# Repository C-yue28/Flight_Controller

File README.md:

<h1>Custom Flight Controller</h1>

<h3>What is it?</h3>
<p>This is a custom flight controller with onboard LiPo charging capabilities and buck converters for 3V bus as well as support for 6 external motors (3 DC, 3 servo) and 7-pin breakout for external sensor array. USB-UART bus for uploading firmware via serial. Internal power paths for limited high-current motor handling; however most motor wiring will most likely have to be done externally due to PCB limitations.</p>

<h3>Why did I make this?</h3>
<p>Flight has always been something that has fascinated me and so far my only experience has been with assembling premade drone kits or glider kits. I want to be able to go out and fly something that I made essentially from scratch. I have this vision of myself standing on the roof, tossing the plane off, and watching it fly up into the sky, and then looking at the camera feed to see the world from up high.</p>

<h3>Main components/features</h3>
<ol>
  <li>ESP32-S3-WROOM-1U - Central processor</li>
  <li>BMS management circuitry; computer is powered by 3S LiPo battery</li>
  <li>IMU (6-axis; accelerometer/gyroscope)</li>
  <li>Pressure sensor (for altitude)</li>
  <li>OV5640 Camera (external)</li>
  <li>Miscellaneous: external 2.4ghz antenna capability; dual USB-C for charging/data; external microSD support</li>
</ol>

<h3>Firmware brief description</h3>
- Modular handling of all sensors with interrupts configured to save battery power
- Verbose error/initialization logging to detect I2C issues
- Ability to log data to microSD card

<h3>Images</h3>

<h3>External sources (for the LSM6DSOX firmware libraries)</h3>

[Base LSM6DS Adafruit library](https://github.com/adafruit/Adafruit_LSM6DS/blob/master/examples/adafruit_lsm6ds_unifiedsensors/adafruit_lsm6ds_unifiedsensors.ino)

### Dependencies of this library:

[Adafruit_BusIO](https://github.com/adafruit/Adafruit_BusIO/tree/master)

[Adafruit_Sensor](https://github.com/adafruit/Adafruit_Sensor/tree/master)

<h3>BOM</h3>

| Item     | Price | Distributor/Supplier |
|----------|-------|----------------------|
| PCB      | 47.9  | JLCPCB               |
| Stencil  | 7.16  | JLCPCB               |
| Shipping | 24.15 | JLCPCB               |
| Total    | 79.21 |                      |

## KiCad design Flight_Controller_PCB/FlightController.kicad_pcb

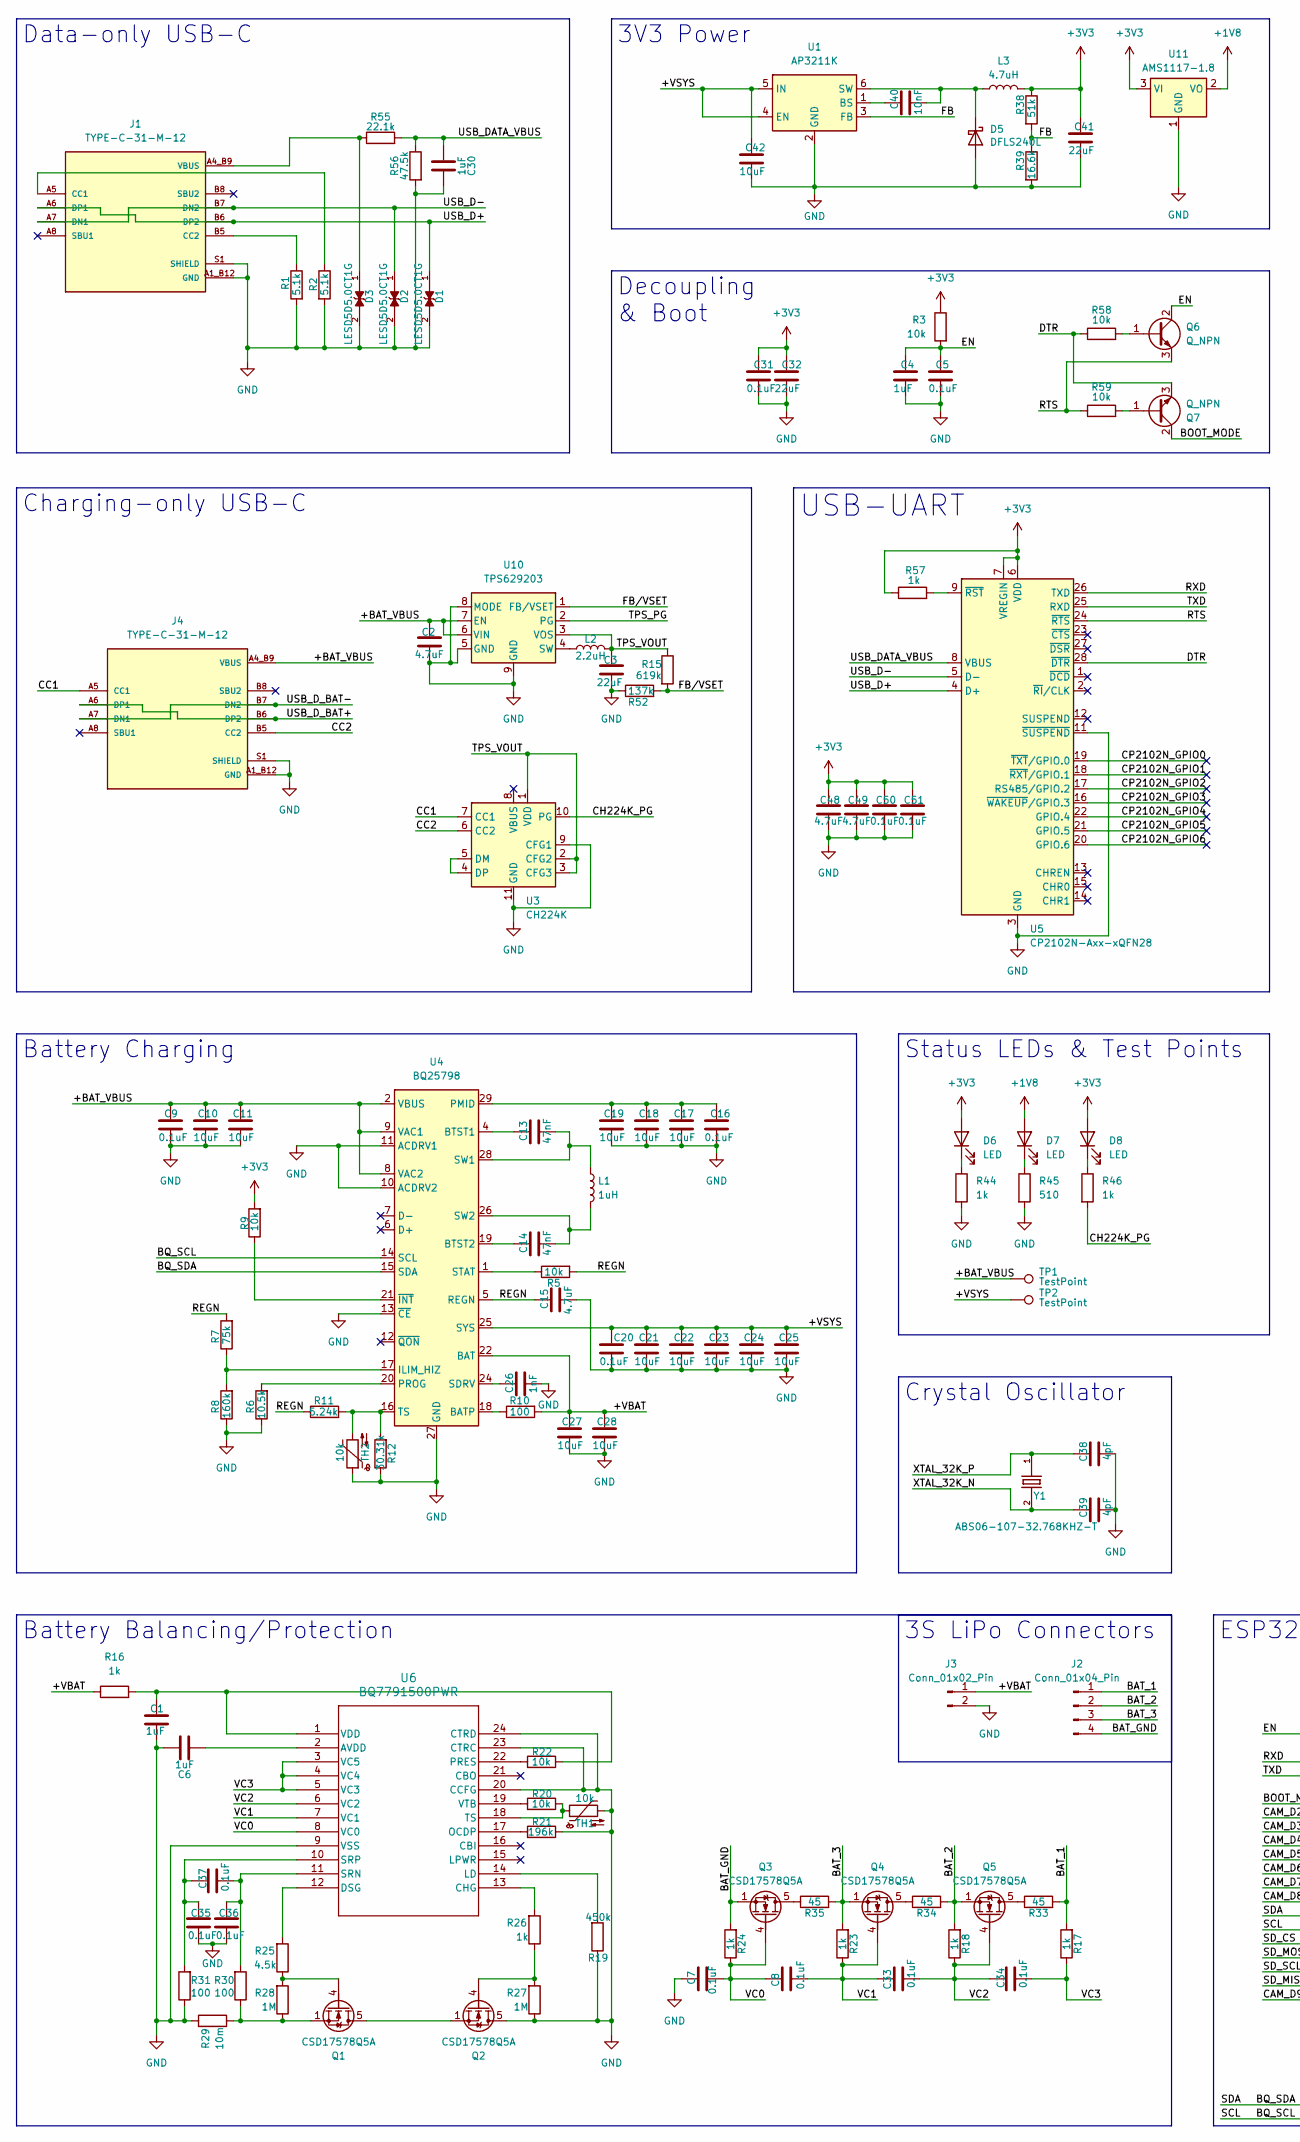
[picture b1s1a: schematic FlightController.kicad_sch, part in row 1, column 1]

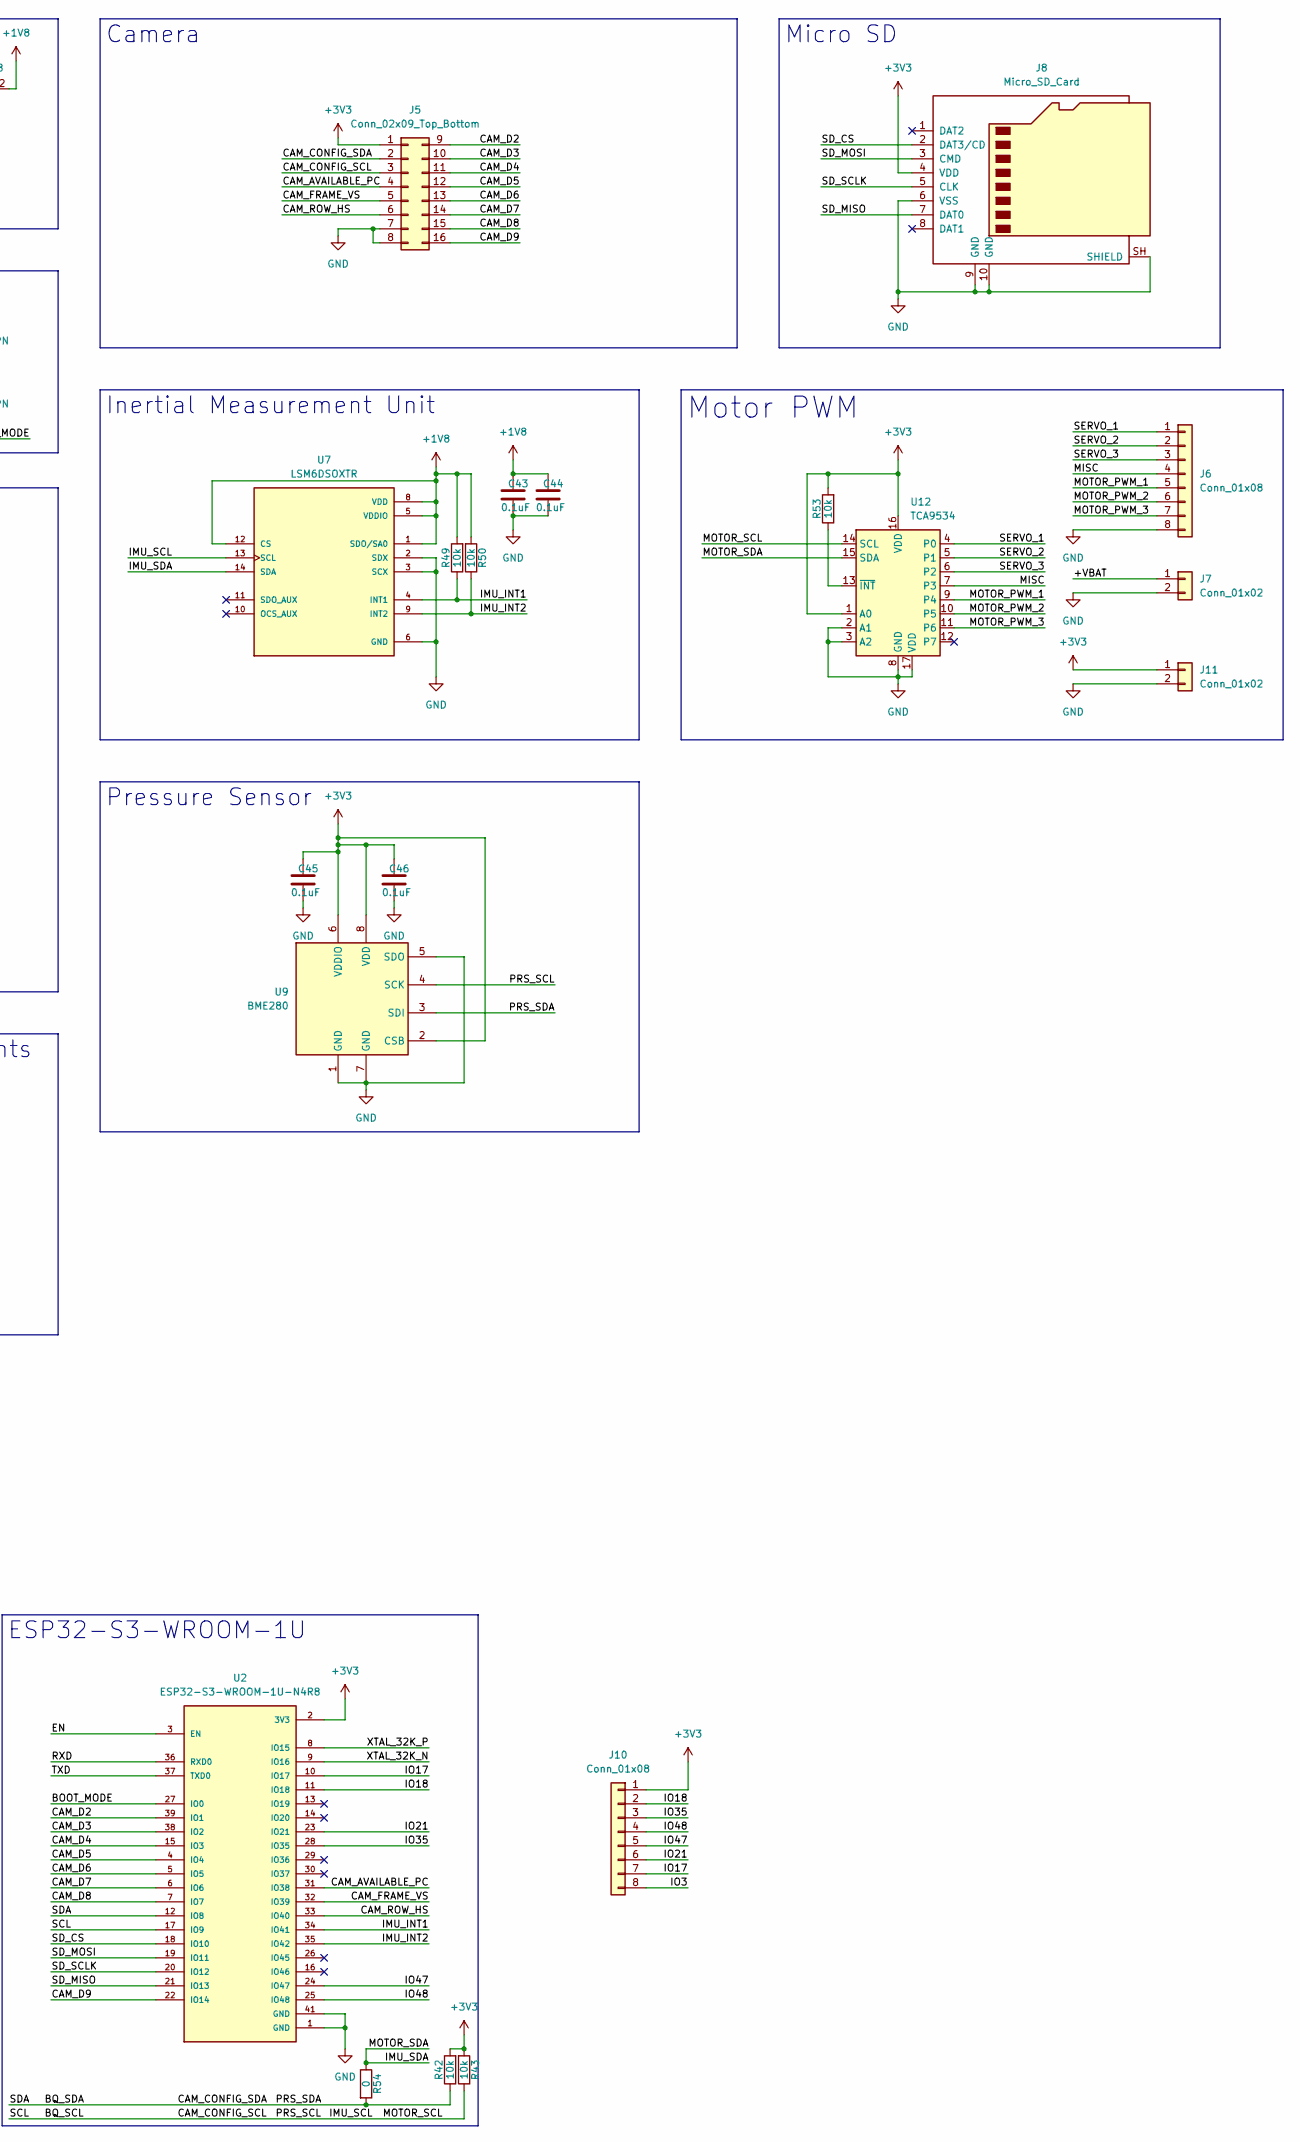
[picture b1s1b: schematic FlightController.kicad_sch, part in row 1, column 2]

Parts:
C1, C4, C6, C30: 1uF; C_0603_1608Metric
C2: 4.7uF; C_1206_3216Metric
C3: 22uF; C_0805_2012Metric
C5, C7, C8, C9, C16, C20, C31, C33, C34, C35, C36, C37, C43, C44, C45, C46, C50, C51: 0.1uF; C_0603_1608Metric
C10, C11, C17, C18, C19, C21, C22, C23, C24, C25, C27, C28, C42: 10uF; C_0603_1608Metric
C13, C14: 47nF; C_0603_1608Metric
C15, C48, C49: 4.7uF; C_0603_1608Metric
C26: 1nF; C_0603_1608Metric
C32, C41: 22uF; C_0603_1608Metric
C38, C39: 4pF; C_0603_1608Metric
C40: 10nF; C_0603_1608Metric
D1, D2, D3: LESD5D5.0CT1G; TVS_LESD5D5.0CT1G; PARTREV O
D5: DFLS240L; D_PowerDI-123
D6, D7, D8: LED; LED_0402_1005Metric
J1, J4: TYPE-C-31-M-12; HRO_TYPE-C-31-M-12; PARTREV 2020.12.08
J2: Conn_01x04_Pin; JST_XH_B4B-XH-A_1x04_P2.50mm_Vertical
J3: Conn_01x02_Pin; AMASS_XT60-M_1x02_P7.20mm_Vertical
J5: Conn_02x09_Top_Bottom; TestPoint_THTPad_2.0x2.0mm_Drill1.0mm
J6, J10: Conn_01x08; TestPoint_THTPad_4.0x4.0mm_Drill2.0mm
J7, J11: Conn_01x02; TestPoint_THTPad_4.0x4.0mm_Drill2.0mm
J8: Micro_SD_Card; microSD_HC_Molex_104031-0811
L1: 1uH; L_0603_1608Metric
L2: 2.2uH; L_1008_2520Metric
L3: 4.7uH; L_Abracon_ASPI-4030S
Q1, Q2, Q3, Q4, Q5: CSD17578Q5A; VSON-8_3.3x3.3mm_P0.65mm_NexFET
Q6, Q7: Q_NPN; SOT-23
R1, R2: 5.1k; R_0402_1005Metric
R3, R5, R9, R20, R22, R42, R43, R49, R50, R53, R58, R59: 10k; R_0402_1005Metric
R6: 10.5k; R_0402_1005Metric
R7: 75k; R_0402_1005Metric
R8: 160k; R_0402_1005Metric
R10, R30, R31: 100; R_0402_1005Metric
R11: 5.24k; R_0402_1005Metric
R12: 30.31k; R_0402_1005Metric
R15: 619k; R_0402_1005Metric
R16, R17, R18, R23, R24, R26, R44, R46, R57: 1k; R_0402_1005Metric
R19: 450k; R_0402_1005Metric
R21: 196k; R_0402_1005Metric
R25: 4.5k; R_0402_1005Metric
R27, R28: 1M; R_0402_1005Metric
R29: 10m; R_0402_1005Metric
R33, R34, R35: 45; R_0805_2012Metric_Pad1.20x1.40mm_HandSolder
R38: 51k; R_0402_1005Metric
R39: 16.6k; R_0402_1005Metric
R45: 510; R_0402_1005Metric
R52: 137k; R_0402_1005Metric
R54: 0; R_0603_1608Metric
R55: 22.1k; R_0402_1005Metric
R56: 47.5k; R_0402_1005Metric
TH1, TH2: 10k; R_0805_2012Metric
TP1, TP2: TestPoint; TestPoint_THTPad_1.5x1.5mm_Drill0.7mm
U1: AP3211K; SOT-23-6
U2: ESP32-S3-WROOM-1U-N4R8; XCVR_ESP32-S3-WROOM-1U-N4R8; PARTREV v1.1; DigiKey_Part_Number 1965-ESP32-S3-WROOM-1U-N4R8CT-ND
U3: CH224K; SSOP-10-1EP_3.9x4.9mm_P1mm_EP2.1x3.3mm
U4: BQ25798; Texas_RQM0029A_VQFN-29_4x4mm_P0.4mm
U5: CP2102N-Axx-xQFN28; QFN-28-1EP_5x5mm_P0.5mm_EP3.35x3.35mm
U6: BQ7791500PWR; PW24_TEX
U7: LSM6DSOXTR; PQFN50P250X300X86-14N; PARTREV 3.0; DigiKey_Part_Number 497-18367-1-ND
U9: BME280; Bosch_LGA-8_2.5x2.5mm_P0.65mm_ClockwisePinNumbering
U10: TPS629203; SOT-583-8
U11: AMS1117-1.8; SOT-223-3_TabPin2
U12: TCA9534; TSSOP-16-1EP_4.4x5mm_P0.65mm
Y1: ABS06-107-32.768KHZ-T; XTAL_ABS06-107-32.768KHZ-T; DigiKey_Part_Number 535-12373-1-ND

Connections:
+1V8: C43.1, C44.1, D7.2 (A), R49.2, R50.2, U7.1 (SDO/SA0), U7.5 (VDDIO), U7.8 (VDD), U7.12 (CS), U11.2 (VO)
+3V3: C31.1, C32.1, C41.1, C45.1, C46.1, C48.1, C49.1, C50.1, C51.1, D6.2 (A), D8.2 (A), J5.1, J8.4 (VDD), J10.1, J11.1, L3.2, R3.1, R9.2, R38.1, R42.2, R43.2, R53.2, R57.1, U2.2 (3V3), U5.6 (VDD), U5.7 (VREGIN), U9.2 (CSB), U9.6 (VDDIO), U9.8 (VDD), U11.3 (VI), U12.1 (A0), U12.16 (VDD)
/+VBAT: C27.1, C28.1, J3.1, J7.1, R10.2, R16.1, U4.22 (BAT), U4.23 (BAT)
/+VSYS: C20.1, C21.1, C22.1, C23.1, C24.1, C25.1, C42.1, TP2.1 (1_1), U1.4 (EN), U1.5 (IN), U4.25 (SYS)
/BAT_1: J2.1, R17.2, R33.2
/BAT_2: J2.2, Q5.1 (S), Q5.2 (S), Q5.3 (S), R18.2, R34.2
/BAT_3: J2.3, Q4.1 (S), Q4.2 (S), Q4.3 (S), R23.2, R35.2
/BAT_GND: J2.4, Q3.1 (S), Q3.2 (S), Q3.3 (S), R24.2
/BOOT_MODE: Q7.2 (C), U2.27 (IO0)
/BQ_SCL: J5.3, R43.1, U2.17 (IO9), U4.14 (SCL), U7.13 (SCL), U9.4 (SCK), U12.14 (SCL)
/BQ_SDA: J5.2, R42.1, R54.2, U2.12 (IO8), U4.15 (SDA), U9.3 (SDI)
/CAM_AVAILABLE_PC: J5.4, U2.31 (IO38)
/CAM_D2: J5.9, U2.39 (IO1)
/CAM_D3: J5.10, U2.38 (IO2)
/CAM_D4: J5.11, U2.15 (IO3)
/CAM_D5: J5.12, U2.4 (IO4)
/CAM_D6: J5.13, U2.5 (IO5)
/CAM_D7: J5.14, U2.6 (IO6)
/CAM_D8: J5.15, U2.7 (IO7)
/CAM_D9: J5.16, U2.22 (IO14)
/CAM_FRAME_VS: J5.5, U2.32 (IO39)
/CAM_ROW_HS: J5.6, U2.33 (IO40)
/CC1: J4.A5 (CC1), U3.7 (CC1)
/CC2: J4.B5 (CC2), U3.6 (CC2)
/CH224K_PG: R46.2, U3.10 (PG)
/CP2102N_GPIO0: U5.19 (~TXT/GPIO.0)
/CP2102N_GPIO1: U5.18 (~RXT/GPIO.1)
/CP2102N_GPIO2: U5.17 (RS485/GPIO.2)
/CP2102N_GPIO3: U5.16 (~WAKEUP/GPIO.3)
/CP2102N_GPIO4: U5.22 (GPIO.4)
/CP2102N_GPIO5: U5.21 (GPIO.5)
/CP2102N_GPIO6: U5.20 (GPIO.6)
/DTR: Q7.3 (E), R58.1, U5.28 (~DTR)
/EN: C4.1, C5.1, Q6.2 (C), R3.2, U2.3 (EN)
/FB: R38.2, R39.1, U1.3 (FB)
/FB/VSET: R15.2, R52.2, U10.1 (FB/VSET)
/IMU_INT1: R49.1, U2.34 (IO41), U7.4 (INT1)
/IMU_INT2: R50.1, U2.35 (IO42), U7.9 (INT2)
/IMU_SDA: R54.1, U7.14 (SDA), U12.15 (SDA)
/IO3: J10.8
/IO17: J10.7, U2.10 (IO17)
/IO18: J10.2, U2.11 (IO18)
/IO21: J10.6, U2.23 (IO21)
/IO35: J10.3, U2.28 (IO35)
/IO47: J10.5, U2.24 (IO47)
/IO48: J10.4, U2.25 (IO48)
/MISC: J6.4, U12.7 (P3)
/MOTOR_PWM_1: J6.5, U12.9 (P4)
/MOTOR_PWM_2: J6.6, U12.10 (P5)
/MOTOR_PWM_3: J6.7, U12.11 (P6)
/REGN: C15.1, R5.2, R7.2, R11.1, U4.5 (REGN)
/RTS: Q6.3 (E), R59.1, U5.24 (~RTS)
/RXD: U2.36 (RXD0), U5.26 (TXD)
/SD_CS: J8.2 (DAT3/CD), U2.18 (IO10)
/SD_MISO: J8.7 (DAT0), U2.21 (IO13)
/SD_MOSI: J8.3 (CMD), U2.19 (IO11)
/SD_SCLK: J8.5 (CLK), U2.20 (IO12)
/SERVO_1: J6.1, U12.4 (P0)
/SERVO_2: J6.2, U12.5 (P1)
/SERVO_3: J6.3, U12.6 (P2)
/TPS_PG: U10.2 (PG)
/TPS_VOUT: C3.1, L2.1, R15.1, U3.1 (VDD), U3.2 (CFG2), U3.3 (CFG3), U10.3 (VOS)
/TXD: U2.37 (TXD0), U5.25 (RXD)
/USB_D+: D1.1, J1.A6 (DP1), J1.B6 (DP2), U5.4 (D+)
/USB_D-: D2.1, J1.A7 (DN1), J1.B7 (DN2), U5.5 (D-)
/USB_DATA_VBUS: C30.2, R55.2, R56.1, U5.8 (VBUS)
/USB_D_BAT+: J4.A6 (DP1), J4.B6 (DP2)
/USB_D_BAT-: J4.A7 (DN1), J4.B7 (DN2)
/VC0: C7.2, C8.2, Q3.4 (G), R24.1, U6.8 (VC0)
/VC1: C8.1, C33.2, Q4.4 (G), R23.1, U6.7 (VC1)
/VC2: C33.1, C34.2, Q5.4 (G), R18.1, U6.6 (VC2)
/VC3: C34.1, R17.1, U6.3 (VC5), U6.4 (VC4), U6.5 (VC3)
/XTAL_32K_N: C39.1, U2.9 (IO16), Y1.2
/XTAL_32K_P: C38.1, U2.8 (IO15), Y1.1
GND: C1.2, C2.2, C3.2, C4.2, C5.2, C6.1, C7.1, C9.2, C10.2, C11.2, C15.2, C16.2, C17.2, C18.2, C19.2, C20.2, C21.2, C22.2, C23.2, C24.2, C25.2, C26.2, C27.2, C28.2, C30.1, C31.2, C32.2, C35.1, C36.1, C38.2, C39.2, C41.2, C42.2, C43.2, C44.2, C45.2, C46.2, C48.2, C49.2, C50.2, C51.2, D1.2, D2.2, D3.2, D5.2 (A), J1.A1_B12 (GND), J1.B1_A12 (GND), J1.S1 (SHIELD), J1.S2 (SHIELD), J1.S3 (SHIELD), J1.S4 (SHIELD), J3.2, J4.A1_B12 (GND), J4.B1_A12 (GND), J4.S1 (SHIELD), J4.S2 (SHIELD), J4.S3 (SHIELD), J4.S4 (SHIELD), J5.7, J5.8, J6.8, J7.2, J8.6 (VSS), J8.9 (GND), J8.10 (GND), J8.SH (SHIELD), J11.2, Q2.5 (D), R1.2, R2.2, R6.1, R8.1, R12.1, R19.1, R21.1, R27.1, R29.2, R31.1, R39.2, R44.2, R45.2, R52.1, R56.2, TH1.2, TH2.1, U1.2 (GND), U2.1 (GND), U2.40 (GND), U2.41 (GND), U2.41_1 (GND), U2.41_2 (GND), U2.41_3 (GND), U2.41_4 (GND), U2.41_5 (GND), U2.41_6 (GND), U2.41_7 (GND), U2.41_8 (GND), U2.41_9 (GND), U3.9 (CFG1), U3.11 (GND), U4.10 (ACDRV2), U4.11 (ACDRV1), U4.13 (~CE), U4.27 (GND), U5.3 (GND), U5.11 (~SUSPEND), U5.29 (GND), U6.9 (VSS), U6.20 (CCFG), U6.23 (CTRC), U6.24 (CTRD), U7.2 (SDX), U7.3 (SCX), U7.6 (GND), U7.7 (GND), U9.1 (GND), U9.5 (SDO), U9.7 (GND), U10.5 (GND), U10.8 (MODE), U10.9 (GND), U11.1 (GND), U12.2 (A1), U12.3 (A2), U12.8 (GND), U12.17 (VDD)
unnamed: C40.2, D5.1 (K), L3.1, U1.6 (SW)
unnamed: D6.1 (K), R44.1
unnamed: D7.1 (K), R45.1
unnamed: D8.1 (K), R46.1
unnamed: J1.A5 (CC1), R2.1
unnamed: J1.B5 (CC2), R1.1
unnamed: Q1.5 (D), Q2.1 (S), Q2.2 (S), Q2.3 (S)
unnamed: Q1.4 (G), R25.1, R28.2
unnamed: Q1.1 (S), Q1.2 (S), Q1.3 (S), R28.1, R29.1, R30.1
unnamed: Q2.4 (G), R26.1, R27.2
unnamed: Q3.5 (D), R35.1
unnamed: Q4.5 (D), R34.1
unnamed: Q5.5 (D), R33.1
unnamed: Q6.1 (B), R58.2
unnamed: Q7.1 (B), R59.2
unnamed: C40.1, U1.1 (BS)
unnamed: U3.4 (DP), U3.5 (DM)
unnamed: R10.1, U4.18 (BATP)
unnamed: C13.1, U4.4 (BTST1)
unnamed: C14.1, U4.19 (BTST2)
unnamed: R7.1, R8.2, U4.17 (ILIM_HIZ)
unnamed: C16.1, C17.1, C18.1, C19.1, U4.29 (PMID)
unnamed: R6.2, U4.20 (PROG)
unnamed: C26.1, U4.24 (SDRV)
unnamed: R5.1, U4.1 (STAT)
unnamed: C13.2, L1.1, U4.28 (SW1)
unnamed: C14.2, L1.2, U4.26 (SW2)
unnamed: R11.2, R12.2, TH2.2, U4.16 (TS)
unnamed: R9.1, U4.21 (~INT)
unnamed: R57.2, U5.9 (~RST)
unnamed: C6.2, U6.2 (AVDD)
unnamed: R26.2, U6.13 (CHG)
unnamed: R25.2, U6.12 (DSG)
unnamed: R19.2, U6.14 (LD)
unnamed: R21.2, U6.17 (OCDP)
unnamed: R22.2, U6.22 (PRES)
unnamed: C36.2, C37.1, R30.2, U6.11 (SRN)
unnamed: C35.2, C37.2, R31.2, U6.10 (SRP)
unnamed: R20.1, TH1.1, U6.18 (TS)
unnamed: C1.1, R16.2, R22.1, U6.1 (VDD)
unnamed: R20.2, U6.19 (VTB)
unnamed: L2.2, U10.4 (SW)
unnamed: R53.1, U12.13 (~INT)

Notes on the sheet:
3S LiPo Connectors
ESP32-S3-WROOM-1U
Micro SD
Motor PWM
Camera
USB-UART
Decoupling & Boot
Data-only USB-C
Inertial Measurement Unit
Pressure Sensor
Battery Balancing/Protection
Battery Charging
3V3 Power
Charging-only USB-C
Crystal Oscillator
Status LEDs & Test Points

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
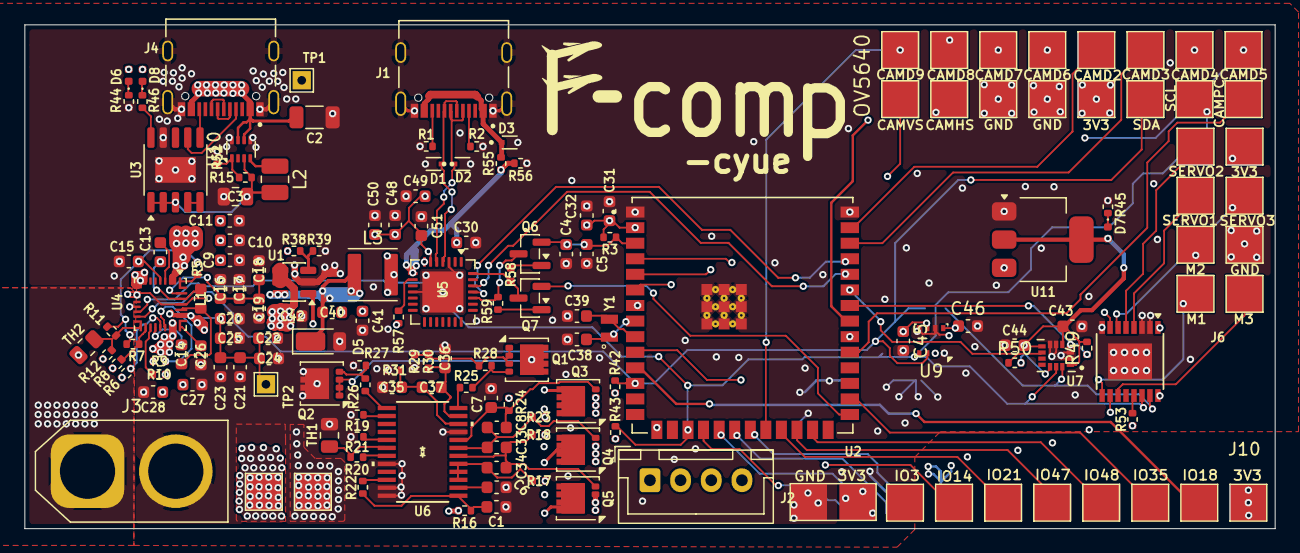
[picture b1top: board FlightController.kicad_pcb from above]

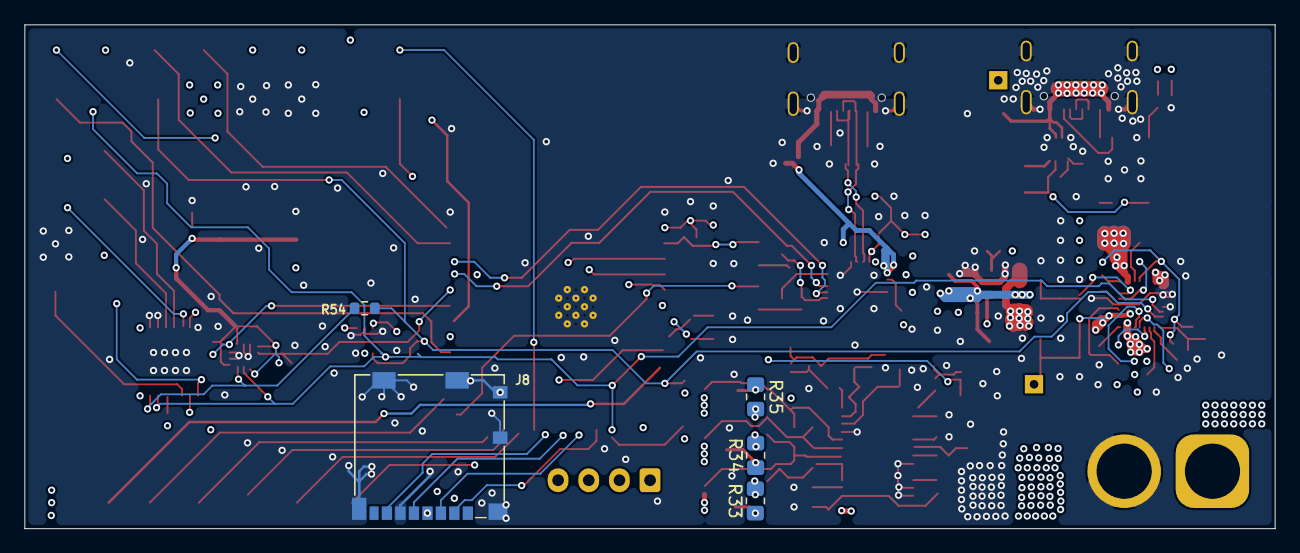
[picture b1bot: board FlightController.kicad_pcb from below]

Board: 6 copper layers, 102.0 x 41.1 mm, 139 parts (5 on the bottom side), 110 nets.

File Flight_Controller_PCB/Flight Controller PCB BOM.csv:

Designator,Footprint,Quantity,Value,URL,Cost,Notes
"C1, C30, C4, C6",0603,4,1uF,https://www.lcsc.com/product-detail/C128624.html,1.3,I may already have these
"C10, C11, C17, C18, C19, C21, C22, C23, C24, C25, C27, C28, C42",0603,13,10uF,https://www.lcsc.com/product-detail/C22367825.html,1.16,I may already have these
"C13, C14",0603,2,47nF,0603B473K500NT | FH | Price | In Stock | LCSC Electronics,0.61,
"C15, C48, C49",0603,3,4.7uF,https://www.lcsc.com/product-detail/C5252400.html?lcsc_vid=R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,0.45,I may already have these
"C16, C20, C31, C33, C34, C35, C36, C37, C43, C44, C45, C46, C5, C50, C51, C7, C8, C9",0603,18,0.1uF,https://www.lcsc.com/product-detail/C125205.html?lcsc_vid=RQ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,0.81,I may already have these
C2,1206,1,4.7uF,https://www.lcsc.com/product-detail/C22399656.html,0.85,
C26,0603,1,1nF,https://www.lcsc.com/product-detail/C44369.html,0.52,
C3,0805,1,22uF,(included below),n/a,I decided to just use a smaller footprint to save some money
"C32, C41",0603,2,22uF,https://www.digikey.com/en/products/detail/samsung-electro-m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,0.64,
"C38, C39",0603,2,4pF,https://www.lcsc.com/product-detail/C1668.html,0.42,
C40,0603,1,10nF,https://www.lcsc.com/product-detail/C100042.html,0.61,
"D1, D2, D3",TVS_LESD5D5.0CT1G,3,LESD5D5.0CT1G,https://www.lcsc.com/product-detail/C5246195.html,0.36,
D5,D_PowerDI-123,1,DFLS240L,,,
"D6, D7, D8",0402,3,LED,https://www.lcsc.com/product-detail/Light-Emitting-Diodes-LE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,0.76,
"J1, J4",HRO_TYPE-C-31-M-12,2,TYPE-C-31-M-12,(I already have these),n/a,
"J10, J6",TestPoint_THTPad_4.0x4.0mm_Drill2.0mm,2,Conn_01x08,n/a,,
"J11, J7",TestPoint_THTPad_4.0x4.0mm_Drill2.0mm,2,Conn_01x02,n/a,,
J2,JST_XH_B4B-XH-A_1x04_P2.50mm_Vertical,1,Conn_01x04_Pin,https://www.lcsc.com/product-detail/C144395.html,0.58,
J3,AMASS_XT60-M_1x02_P7.20mm_Vertical,1,Conn_01x02_Pin,https://www.lcsc.com/product-detail/C98733.html,0.4,
J5,TestPoint_THTPad_2.0x2.0mm_Drill1.0mm,1,Conn_02x09_Top_Bottom,n/a,,
J8,microSD_HC_Molex_104031-0811,1,Micro_SD_Card,https://www.lcsc.com/product-detail/C585350.html,0.68,
L1,0603,1,1uH,https://www.lcsc.com/product-detail/C5443610.html,0.42,
L2,1008,1,2.2uH,https://www.digikey.com/en/products/detail/shenzhen-sunlord-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,0.33,
L3,L_Abracon_ASPI-4030S,1,4.7uH,https://www.digikey.com/en/products/detail/abracon-llc/ASPI-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,0.27,
"Q1, Q2, Q3, Q4, Q5",VSON-8_3.3x3.3mm_P0.65mm_NexFET,5,CSD17578Q5A,https://www.lcsc.com/product-detail/C2871447.html,2.41,
"Q6, Q7",SOT-23,2,Q_NPN,https://www.lcsc.com/product-detail/C49581.html,0.79,
"R1, R2",0402,2,5.1k,https://www.digikey.com/en/products/detail/yageo/RC0402FR-07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,0.2,
"R10, R30, R31",0402,3,100,https://www.digikey.com/en/products/detail/vishay-dale/RCA04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,0.3,
R11,0402,1,5.24k,https://www.digikey.com/en/products/detail/bourns-inc/CR0402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,0.1,
R12,0402,1,30.31k,https://www.digikey.com/en/products/detail/vishay-dale/RCS04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,0.13,
R15,0402,1,619k,https://www.digikey.com/en/products/detail/stackpole-electro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,0.1,
"R16, R17, R18, R23, R24, R26, R44, R46, R57",0402,9,1k,https://www.digikey.com/en/products/detail/vishay/MCS04020C1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,0.28,I may already have these
R19,0402,1,450k,https://www.digikey.com/en/products/detail/vishay-dale/CRCW0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,0.1,
"R20, R22, R3, R42, R43, R49, R5, R50, R53, R58, R59, R9",0402,12,10k,https://www.digikey.com/en/products/detail/vishay-dale/RCA04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,0.66,I may already have these
R21,0402,1,196k,https://www.digikey.com/en/products/detail/stackpole-electro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,0.1,
R25,0402,1,4.5k,http://digikey.com/en/products/detail/vishay-dale/TNPW04024K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,0.26,
"R27, R28",0402,2,1M,https://www.digikey.com/en/products/detail/yageo/RC0402FR-07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,0.2,
R29,0402,1,10m,https://www.digikey.com/en/products/detail/thin-film-technol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,0.28,
"R33, R34, R35",0805,3,45,"MBB02070C4539FRP00 (1W, 45.3 OHM): https://www.mouser.com/c/passive-components/resistors/?power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",1.14,
R38,0402,1,51k,https://www.digikey.com/en/products/detail/stackpole-electro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,0.1,
R39,0402,1,16.6k,https://www.digikey.com/en/products/detail/vishay-dale/CRCW0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,0.1,
R45,0402,1,510,https://www.digikey.com/en/products/detail/koa-speer-electro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,0.1,
R52,0402,1,137k,https://www.digikey.com/en/products/detail/yageo/RC0402FR-07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,0.1,
R54,0603,1,0,n/a,,
R55,0402,1,22.1k,https://www.digikey.com/en/products/detail/yageo/RT0402FRE07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,0.1,
R56,0402,1,47.5k,https://www.digikey.com/en/products/detail/yageo/RC0402FR-07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,0.1,
R6,0402,1,10.5k,https://www.digikey.com/en/products/detail/yageo/RT0402FRE07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,0.1,
R7,0402,1,75k,https://www.digikey.com/en/products/detail/yageo/RT0402DRE07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,0.1,
R8,0402,1,160k,https://www.digikey.com/en/products/detail/stackpole-electro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,0.1,
"TH1, TH2",0805,2,10k,https://www.digikey.com/en/products/detail/tdk/B57471V2103J0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,0.62,
"TP1, TP2",TestPoint_THTPad_1.5x1.5mm_Drill0.7mm,2,TestPoint,n/a,,
U1,SOT-23-6,1,AP3211K,https://www.digikey.com/en/products/detail/diodes-incorporat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,0.25,I may already have this
U10,SOT-583-8,1,TPS629203,https://www.digikey.com/en/products/detail/texas-instruments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,1.08,
U11,SOT-223-3_TabPin2,1,AMS1117-1.8,https://www.digikey.com/en/products/detail/evvo/AMS1117-1-8/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,0.3,
U12,TSSOP-16-1EP_4.4x5mm_P0.65mm,1,TCA9534,https://www.digikey.com/en/products/detail/texas-instruments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,1.53,
U2,XCVR_ESP32-S3-WROOM-1U-N4R8,1,ESP32-S3-WROOM-1U-N4R8,https://www.digikey.com/en/products/detail/espressif-systems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,6.76,
U3,SSOP-10-1EP_3.9x4.9mm_P1mm_EP2.1x3.3mm,1,CH224K,https://www.lcsc.com/product-detail/C970725.html,0.62,
U4,Texas_RQM0029A_VQFN-29_4x4mm_P0.4mm,1,BQ25798,https://www.digikey.com/en/products/detail/texas-instruments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,5.2,
U5,QFN-28-1EP_5x5mm_P0.5mm_EP3.35x3.35mm,1,CP2102N-Axx-xQFN28,https://www.digikey.com/en/products/detail/silicon-labs/CP21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,5.1,
U6,PW24_TEX,1,BQ7791500PWR,https://www.digikey.com/en/products/detail/texas-instruments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,2.05,
U7,PQFN50P250X300X86-14N,1,LSM6DSOXTR,https://estore.st.com/en/lsm6dsotr-cpn.html,5.32,LSM6DSOTR
U9,Bosch_LGA-8_2.5x2.5mm_P0.65mm_ClockwisePinNumbering,1,BME280,https://www.digikey.com/en/products/detail/bosch-sensortec/B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,4,
Y1,XTAL_ABS06-107-32.768KHZ-T,1,ABS06-107-32.768KHZ-T,https://www.digikey.com/en/products/detail/abracon-llc/ABS06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,0.83,
,,,,,52.78,

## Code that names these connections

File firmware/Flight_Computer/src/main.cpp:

#include <Arduino.h>
#include <Wire.h>
#include <SD.h>
#include <SPI.h>

// Personal libraries
#include <BQ25798.h>
#include <TCA9534.h>
#include <OV5640.h>
#include <BME280.h>

// Open-source libraries
#include <Adafruit_LSM6DSOX.h>

#define ESP32_ADDR 0x67

// I2C pins

#define SDA 8
#define SCL 9

#define NUM_I2C_DEVICES 5
#define MAX_I2C_INIT_LOOPS 10

// External SD card

#define SD_CS 10
#define SD_MOSI 11
#define SD_SCK 12
#define SD_MISO 13

// Camera: OV5640

#define CAM_D2 1
#define CAM_D3 2
#define CAM_D4 3
#define CAM_D5 4
#define CAM_D6 5
#define CAM_D7 6
#define CAM_D8 7
#define CAM_D9 14
#define CAM_AVAIL_PC 38
#define CAM_FRAME_VS 39
#define CAM_ROW_HS 40

// IMU: LSM6DSOX
#define IMU_I2C_ADDR 0b1101011

#define IMU_INT1 41
#define IMU_INT2 42

// Motor handling
#define SERVO_1 0
#define SERVO_2 1
#define SERVO_3 2
#define MOTOR_1 4
#define MOTOR_2 5
#define MOTOR_3 6

#define PWM_FREQUENCY 1 // 1 tick, or 1 ms per bit on the output lines to ESC

// I2C  

BQ25798 charger(&Wire);
TCA9534 motorController(&Wire);
BME280 bme280(&Wire);
Adafruit_LSM6DSOX imu;
Adafruit_Sensor *imu_temp, *imu_gyro, *imu_accel;

sensors_vec_t rotation;
sensors_vec_t acceleration;
sensors_event_t imu_temp_event;

TaskHandle_t pwmHandle = NULL;

typedef struct {
  uint8_t pin;
  float pwm_duty;
} motorControlConfig;

bool initI2C();
int detectI2CDevices();

bool writeFile(const char *path, const char *data, bool overwrite = false);
uint8_t* readFile(const char *path);

void readIMUData(uint8_t intNum);
void outputPWM(void *pvParameters);

void setup() {

  Serial.begin(115200);
  while (!Serial);

  Serial.print("Serial initialized\n");

  if (!initI2C()) {
    Serial.println("I2C initialization failed");
    return;
  }
  Serial.println("I2C initialized");

  // SD card

  if (!SD.begin(SD_CS)) {
    Serial.println("SD initialization failed");
    return;
  } else {
    Serial.println("SD initialized successfully");
  }

  // run the motors at 25% speed
  motorControlConfig* initial_pwm_config = new motorControlConfig();
  initial_pwm_config->pwm_duty = 0.25;
  for (int i = MOTOR_1; i < MOTOR_3; i++) {
    initial_pwm_config->pin = i;
    xTaskCreatePinnedToCore(outputPWM, "PWM", 4096, (void*)initial_pwm_config, 1, NULL, 0);
  }

}

// Unit tests

/* OV5640

void loop() {
  camera_fb_t *fb = esp_camera_fb_get();
  
  if (!fb) {
      Serial.println("Camera capture failed!");
      delay(1000);
      return;
  }

  Serial.printf("Captured image! Size: %d bytes, Width: %d, Height: %d\n", fb->len, fb->width, fb->height);

  esp_camera_fb_return(fb); 
  
  delay(100); 
}

*/

/* Motors

void loop() {
  motorControlConfig* cfg = new motorControlConfig();
  cfg->pwm_duty = 0.5;
  for (int i = MOTOR_1; i < MOTOR_3; i++) {
    cfg->pin = i;
    xTaskCreatePinnedToCore(outputPWM, "PWM", 4096, cfg, 1, NULL, 0);
  }
  
  cfg->pwm_duty = 0.0;
  for (int i = MOTOR_1; i < MOTOR_3; i++) {
    cfg->pin = i;
    xTaskCreatePinnedToCore(outputPWM, "PWM", 4096, cfg, 1, NULL, 0);
  }
}

*/

/* BME280

void loop() {
  Serial.printf("Temperature: %f C\n", bme280.getTemperature());
  Serial.printf("Pressure: %f Pa\n", bme280.getPressure());
  Serial.printf("Humidity: %f %%\n", bme280.getHumidity());
  vTaskDelay(2000 / portTICK_PERIOD_MS);
}

*/

/* IMU

void loop() {
  Serial.printf("Temperature: %f C\n", altimeter.getTemperature() + imu_temp_event.temperature);
  Serial.printf("Rotation: %f rad/s, %f rad/s, %f rad/s\n", rotation.x, rotation.y, rotation.z);
  Serial.printf("Acceleration: %f m/s^2, %f m/s^2, %f m/s^2\n", acceleration.x, acceleration.y, acceleration.z);
  vTaskDelay(2000 / portTICK_PERIOD_MS);
}

*/

bool initI2C() {
  bool success_I2C = Wire.begin(SDA, SCL);
  if (success_I2C) {
    Serial.println("I2C initialized");
  } else {
    Serial.println("I2C initialization failed");
    return false;
  }

  int numDevices = detectI2CDevices();
  int loops = 0;
  while (numDevices < NUM_I2C_DEVICES) {
    Serial.printf("%d devices found\n", numDevices);
    Serial.println("Not enough I2C devices found, rechecking in 5 seconds");
    delay(5000);
    numDevices = detectI2CDevices();
    loops++;
    if (loops > MAX_I2C_INIT_LOOPS) {
      Serial.println("Max I2C init loops reached, stopping program");
      return false;
    }
  }
  Serial.printf("Successfully detected %d devices!\n", numDevices);

  // I2C device initialization

  // BQ25798

  if (charger.begin()) {
    Serial.println("BQ25798 initialized");
  } else {
    Serial.println("BQ25798 initialization failed");
    return false;
  }

  if (charger.initialize3SDefaults()) {
    Serial.println("BQ25798 3S defaults initialized");
  } else {
    Serial.println("BQ25798 3S defaults initialization failed");
    return false;
  }

  // OV5640

  if (initializeCamera(
    CAM_D2, CAM_D3, CAM_D4, CAM_D5,
    CAM_D6, CAM_D7, CAM_D8, CAM_D9,
    CAM_AVAIL_PC, CAM_FRAME_VS, CAM_ROW_HS,
    SDA, SCL,
    -1, -1
  )) {
    Serial.println("OV5640 initialized");
  } else {
    Serial.println("OV5640 initialization failed");
    return false;
  }

  // TCA9534
  motorController.begin();
  Serial.println("TCA9534 initialized");

  // BME280
  bme280.begin();
  Serial.println("BME280 initialized");

  // IMU
  if (!imu.begin_I2C(IMU_I2C_ADDR)) {
    Serial.println("Failed to initialize IMU!");
    return false;
  }
  Serial.println("IMU initialized");

  imu.configIntOutputs(true, true);
  imu.configInt1(true, true, false, false, false);
  imu.configInt2(false, false, true);

  pinMode(IMU_INT1, OUTPUT_OPEN_DRAIN | INPUT);
  pinMode(IMU_INT2, OUTPUT_OPEN_DRAIN | INPUT);

  attachInterrupt(digitalPinToInterrupt(IMU_INT1), []() { readIMUData(0x00); }, LOW);
  attachInterrupt(digitalPinToInterrupt(IMU_INT2), []() { readIMUData(0x01); }, LOW);

  Serial.println("IMU interrupts configured");

  imu_temp = imu.getTemperatureSensor();
  imu_temp->printSensorDetails();

  imu_accel = imu.getAccelerometerSensor();
  imu_accel->printSensorDetails();

  imu_gyro = imu.getGyroSensor();
  imu_gyro->printSensorDetails();

  Serial.println("IMU sensors configured");

  return true;

}

int detectI2CDevices() {

  byte error, address;
  int nDevices = 0;

  Serial.println("Scanning for devices...");

  for (address = 1; address < 127; address++) {
    Wire.beginTransmission(address);
    error = Wire.endTransmission();

    if (error == 0) {
      Serial.print("I2C device found at address 0x");
      Serial.println(address, HEX);
      nDevices++;
    } else if (error == 4) {
      Serial.print("Unknown error at address 0x");
      Serial.println(address, HEX);
    }
  }

  return nDevices;

}

bool writeFile(const char *path, const char *data, bool overwrite) {
  Serial.printf("Writing to file: %s\n", path);
  File file = SD.open(path, FILE_WRITE);
  if (file) {
    file.print(data);
    file.close();
    Serial.println("Write succeeded");
    return true;
  } else {
    Serial.println("Failed to write");
    return false;
  }
}


uint8_t* readFile(const char *path) {
  Serial.printf("Reading file: %s\n", path);
  File file = SD.open(path);
  size_t len = file.size();
  uint8_t* buffer = (uint8_t*)malloc(len+1);
  if (file) {
    file.read(buffer, len);
    buffer[len] = '\0';
    file.close();
  } else {
    Serial.println("Failed to read");
    return NULL;
  }
  return buffer;
}

void readIMUData(uint8_t intNum) {
  Serial.printf("IMU interrupt %d triggered\n", intNum+1);
  if (intNum == 0x00) {
    sensors_event_t gyro;
    imu_temp->getEvent(&imu_temp_event);
    imu_gyro->getEvent(&gyro);

    rotation = gyro.gyro;

    Serial.printf("Temperature: %.2f C\n", imu_temp_event.temperature);
    Serial.printf("Gyro: %.2f rad/s, %.2f rad/s, %.2f rad/s\n", rotation.x, rotation.y, rotation.z);
  } else {
    sensors_event_t accel;
    imu_accel->getEvent(&accel);

    acceleration = accel.acceleration;

    Serial.printf("Acceleration: %.2f m/s^2, %.2f m/s^2, %.2f m/s^2\n", acceleration.x, acceleration.y, acceleration.z);
  }
}

void outputPWM(void* pvParameters) {
  motorControlConfig* temp_config = (motorControlConfig*)pvParameters;
  motorControlConfig config;
  config.pin = temp_config->pin;
  config.pwm_duty = temp_config->pwm_duty;
  // Send 8-bit PWM after sending arbitrary 8-bit address - change to 4-bit later?
 
  TickType_t xLastWakeTime = xTaskGetTickCount();

  for (int i = 0; i < 8; i++) {
    motorController.digitalWrite(config.pin, (ESP32_ADDR >> i) & 0x01);
    vTaskDelayUntil(&xLastWakeTime, PWM_FREQUENCY);
  }
  
  uint8_t pwm_bits = (uint8_t)(config.pwm_duty * 255);
  xLastWakeTime = xTaskGetTickCount();

  for (int i = 0; i < 8; i++) {
    motorController.digitalWrite(config.pin, (pwm_bits >> i) & 0x01);
    vTaskDelayUntil(&xLastWakeTime, PWM_FREQUENCY);
  }

  motorController.digitalWrite(config.pin, LOW);
}

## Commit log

2026-05-10 Gitignore
2026-05-10 First flight controller PCB commit
2026-06-19 Finished building BQ25798 library, compile successful
2026-06-19 OV5640 configuration completed, build successful
2026-06-21 Sourced LSM6DSOX library from GitHub and wrote basic data-gathering firmware, wrote library for pressure sensor, fixed compile issues
2026-06-21 Added motor control logic, implemented digital PWM, wrote unit tests, added data logging and verbose initialization logging
2026-06-21 Added media, added STEP file of PCB
2026-06-21 Rename images
2026-06-21 Add media
2026-06-21 Add external sources
2026-06-26 Replaced MPL altimeter with BME280 pressure/temp/humidity sensor
2026-06-26 Add BOM
2026-06-26 Finalize for submission and add BOM
